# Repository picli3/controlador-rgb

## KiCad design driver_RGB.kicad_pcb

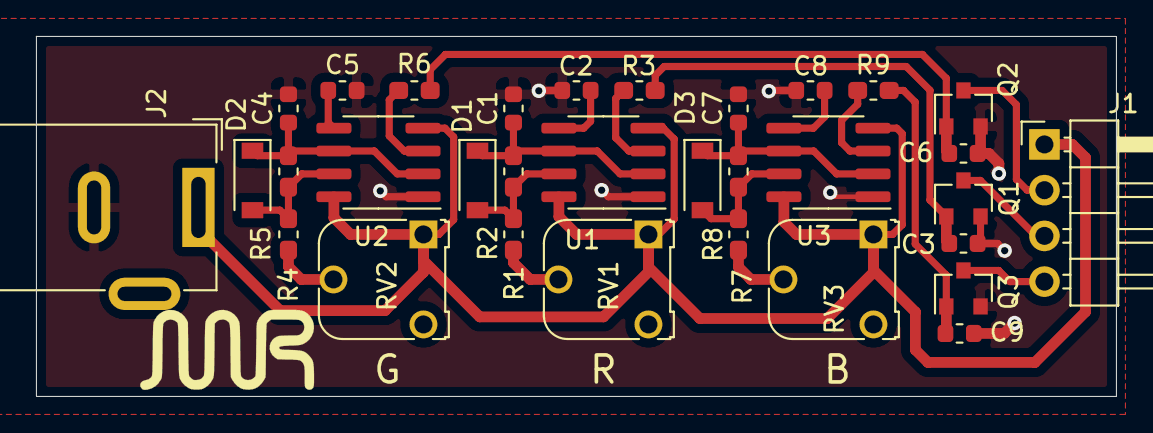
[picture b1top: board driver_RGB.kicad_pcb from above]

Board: 2 copper layers, 60.0 x 20.0 mm, 32 parts (0 on the bottom side), 23 nets.

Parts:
C1, C4, C7: C; C_0603_1608Metric
C2, C3, C5, C6, C8, C9: 100nF; C_0603_1608Metric
D1, D2, D3: MBR0580S1-7; D_SOD-123
J1: OUT; PinHeader_1x04_P2.54mm_Horizontal
J2: Jack-DC; BarrelJack_Wuerth_6941xx301002
Q1, Q2, Q3: MMBT3904LT1G; SOT-23
R1, R2, R3, R5, R6, R7, R8, R9: 1k; R_0603_1608Metric_Pad1.05x0.95mm_HandSolder
R4: 100; R_0603_1608Metric_Pad1.05x0.95mm_HandSolder
RV1, RV2, RV3: 1k; Potentiometer_Runtron_RM-065_Vertical
U1, U2, U3: NE555; SOIC-8-1EP_3.9x4.9mm_P1.27mm_EP2.29x3mm

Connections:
+12V: J1.1, J2.1, RV1.1, RV2.1, RV3.1, U1.4, U1.8, U2.4, U2.8, U3.4, U3.8
/BLUE/BLUE: J1.4, Q3.3
/GREEN/GREEN: J1.2, Q2.3
/RED/RED: J1.3, Q1.3
GND: C1.2, C2.2, C3.2, C4.2, C5.2, C6.2, C7.2, C8.2, C9.2, J2.2, Q1.2, Q2.2, Q3.2, U1.1, U2.1, U3.1
unnamed: C1.1, D1.1, R2.2, U1.2, U1.6
unnamed: C2.1, U1.5
unnamed: C3.1, Q1.1, R3.1
unnamed: C4.1, D2.1, R5.2, U2.2, U2.6
unnamed: C5.1, U2.5
unnamed: C6.1, Q2.1, R6.1
unnamed: C7.1, D3.1, R8.2, U3.2, U3.6
unnamed: C8.1, U3.5
unnamed: C9.1, Q3.1, R9.1
unnamed: D1.2, R1.2, R2.1, U1.7
unnamed: D2.2, R4.2, R5.1, U2.7
unnamed: D3.2, R7.2, R8.1, U3.7
unnamed: R1.1, RV1.2
unnamed: R3.2, U1.3
unnamed: R4.1, RV2.2
unnamed: R6.2, U2.3
unnamed: R7.1, RV3.2
unnamed: R9.2, U3.3

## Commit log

2020-10-10 version 1 terminada
2020-12-20 agregando esquematico pdf
